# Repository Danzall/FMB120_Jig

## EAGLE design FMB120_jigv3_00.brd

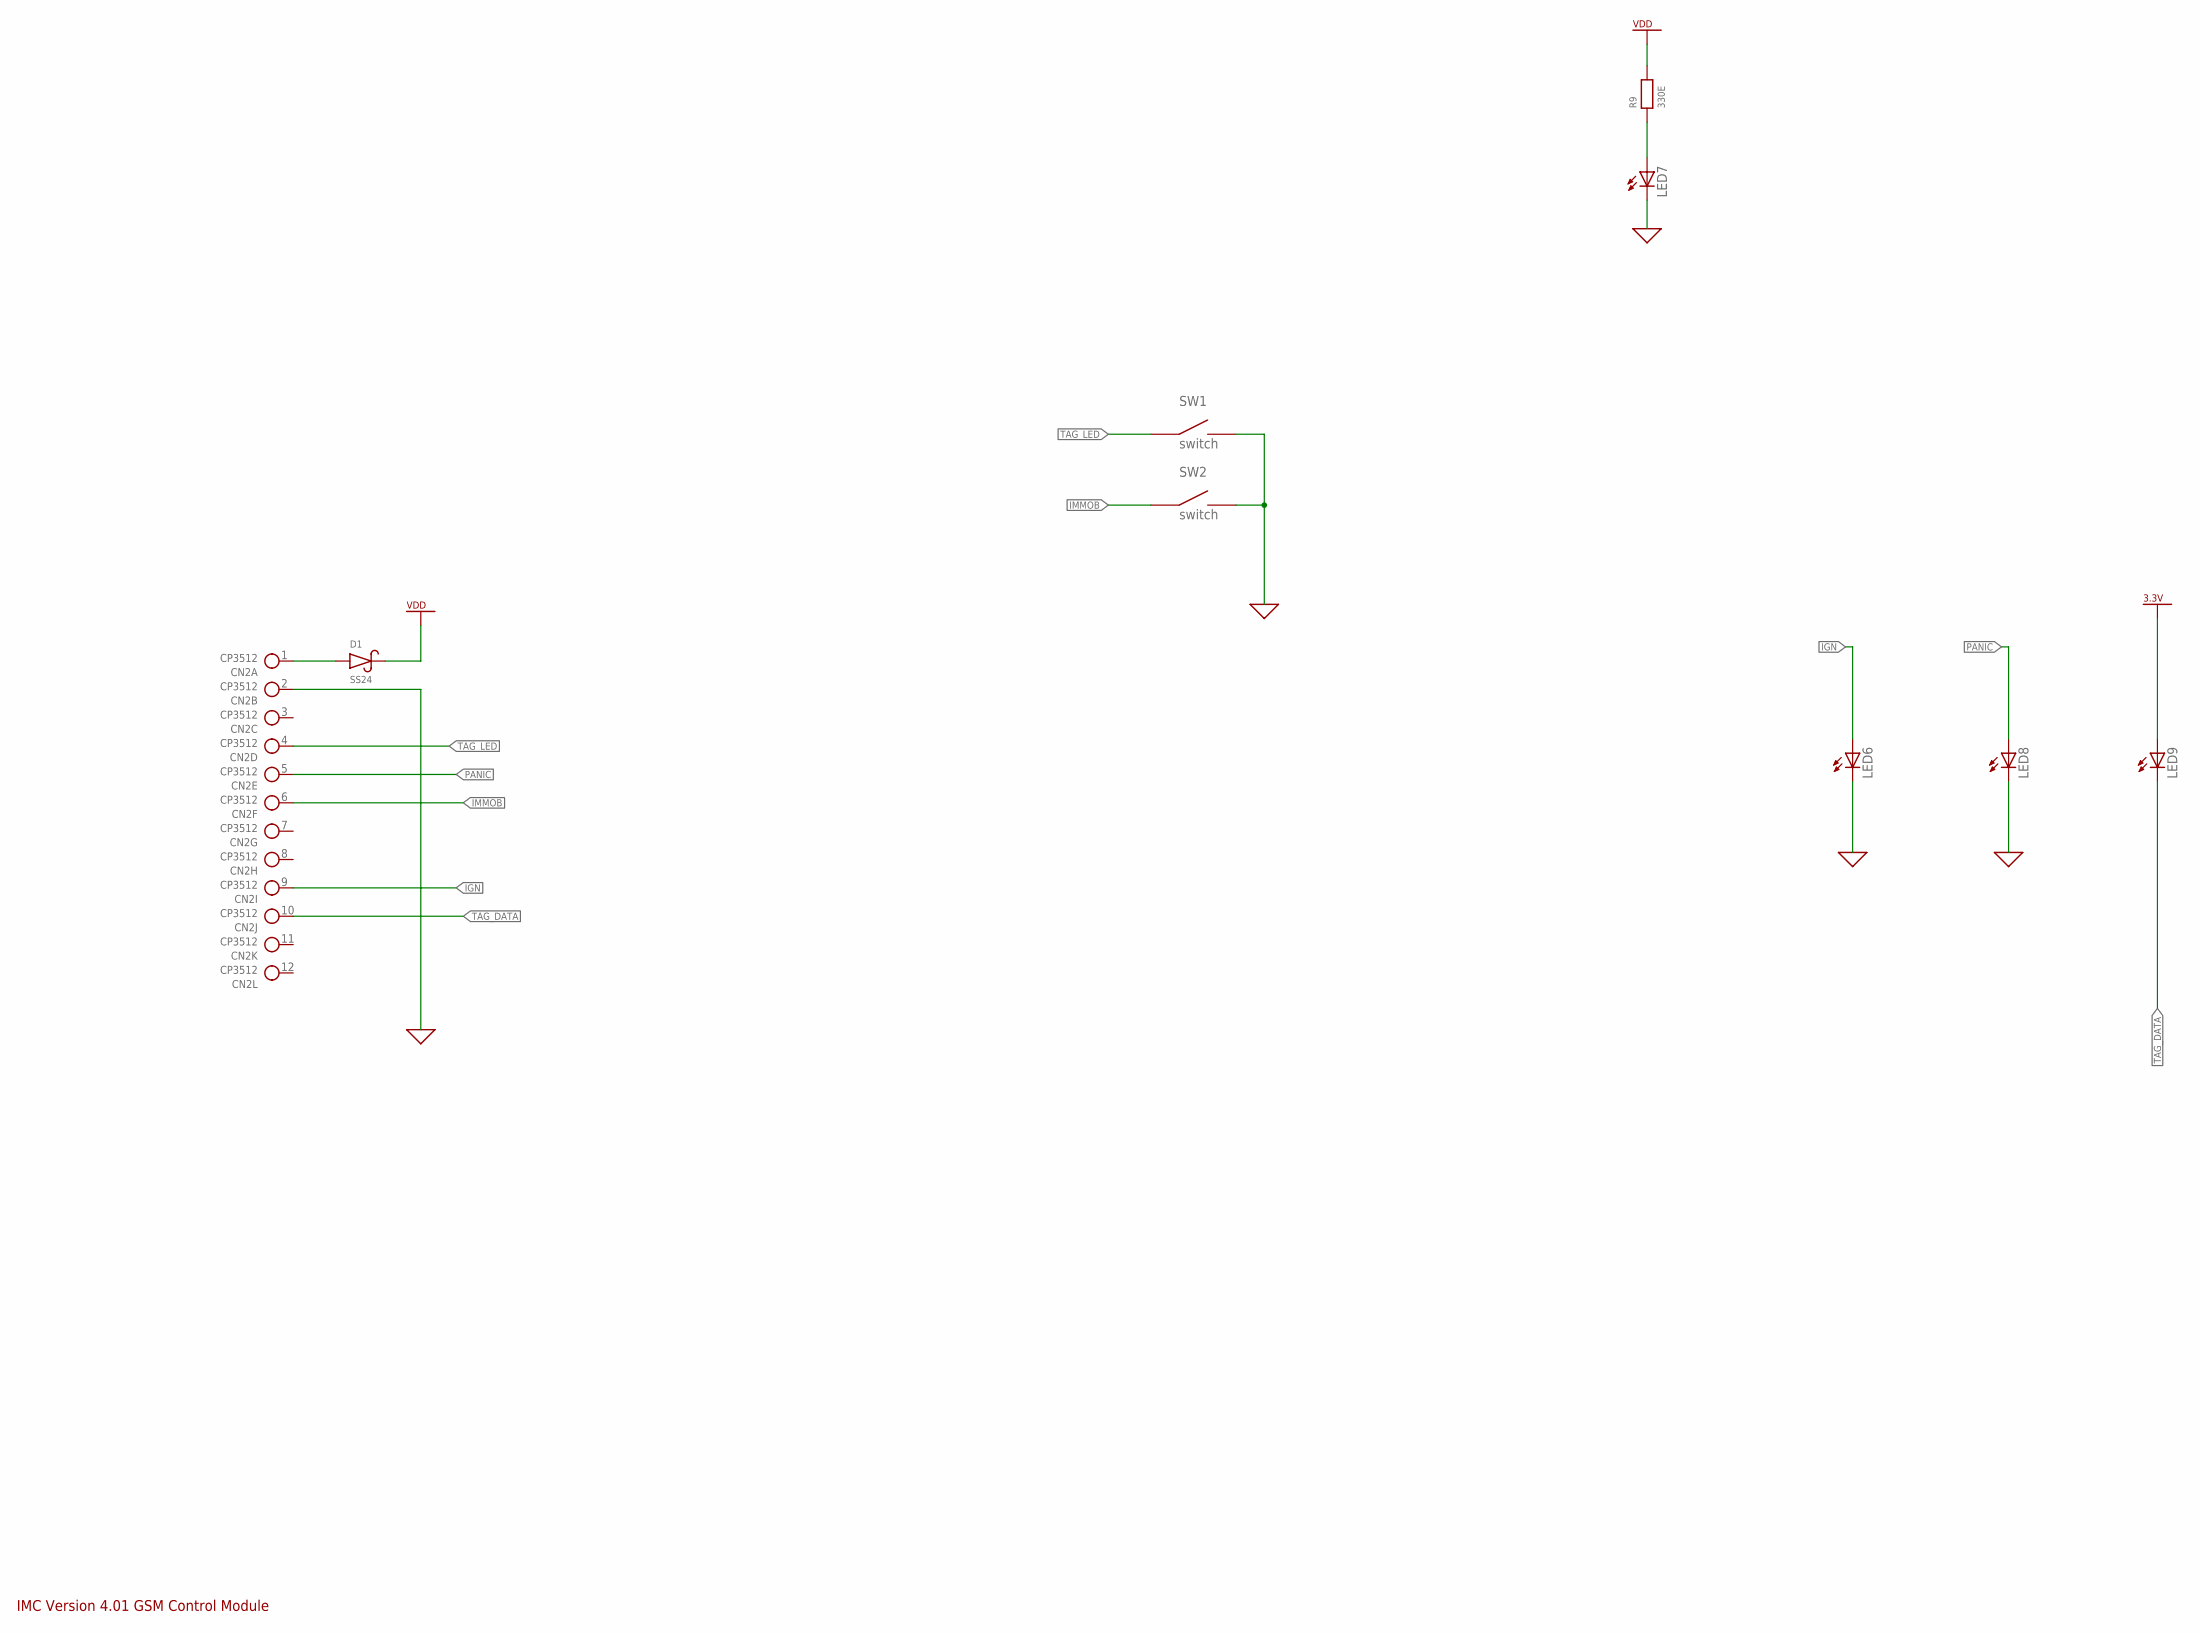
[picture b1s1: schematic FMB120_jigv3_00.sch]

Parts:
CN2: CP3512; CP3512_BLU
D1: SS24; SMB
LED6, LED7, LED8, LED9: LED3MM
R9: 330E; R0603
SW1, SW2: switch; SIL_2

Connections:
3.3V: LED9.A
GND: CN2.2, LED6.K (C), LED7.K (C), LED8.K (C), SW1.2, SW2.2
IGN: CN2.9, LED6.A
IMMOB: CN2.6, SW2.1
unnamed: CN2.1, D1.A
unnamed: LED7.A, R9.1
PANIC: CN2.5, LED8.A
TAG_DATA: CN2.10, LED9.K (C)
TAG_LED: CN2.4, SW1.1
VDD: D1.C (K), R9.2

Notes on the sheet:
IMC Version 4.01 GSM Control Module

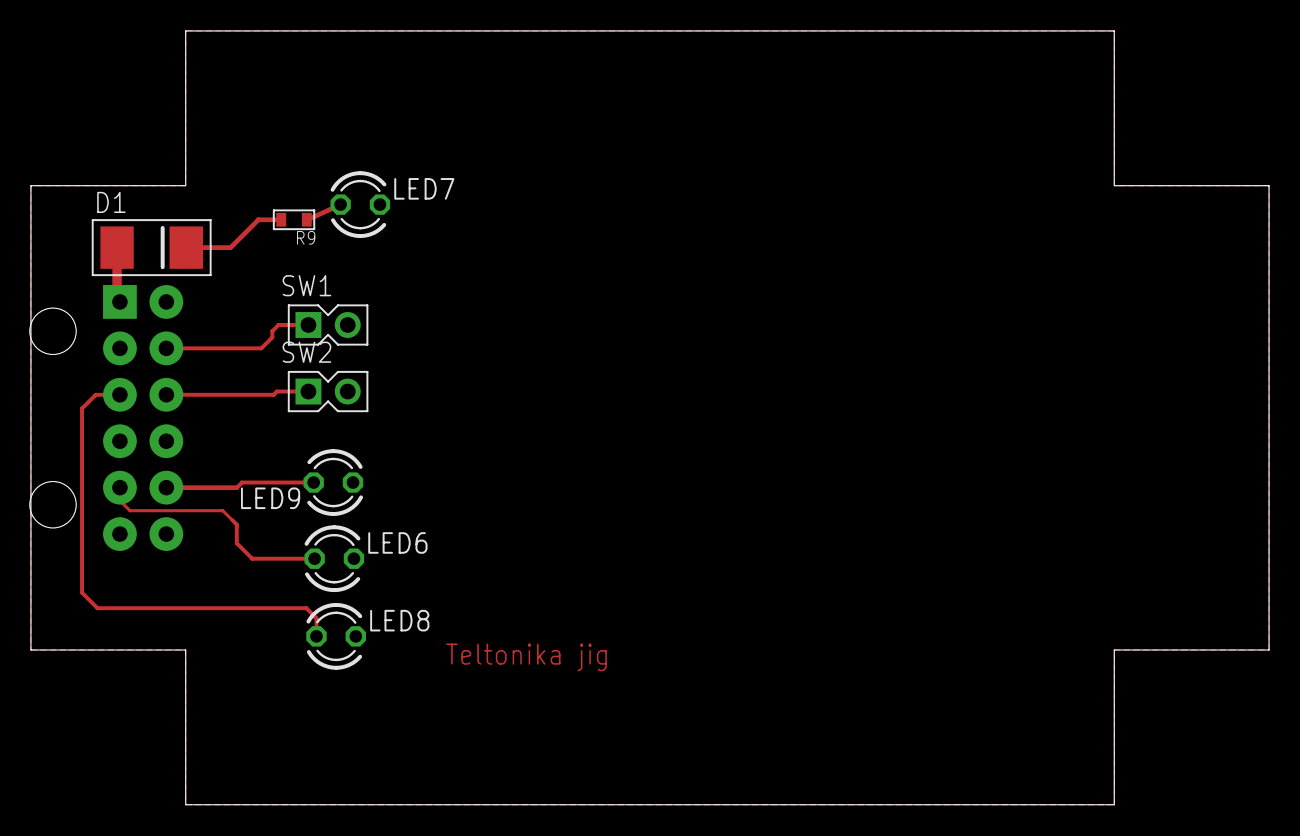
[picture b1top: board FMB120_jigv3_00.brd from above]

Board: 2 copper layers, 80.0 x 50.0 mm, 9 parts (1 on the bottom side), 9 nets.

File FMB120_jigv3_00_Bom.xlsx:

Qty | Value | Device | Package | Parts | Description
4 |  | LED3MM | LED3MM | LED6, LED7, LED8, LED9 | LED
1 | 330E | CHIP-RESISTOR_330E | 603 | 9 | Chip Resistor
1 | CP3512 | 12-WAY_THRU_BLU | CP3512_BLU | CN2
1 | SS24 | DIODE-SHOTKY_SS24 | SMB | D1 | Shotky Diode
2 | PBS-105 | SWITCH_PM | SIL_2 | SW1, SW2

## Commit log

2022-02-17 moved power LED up 1mm
